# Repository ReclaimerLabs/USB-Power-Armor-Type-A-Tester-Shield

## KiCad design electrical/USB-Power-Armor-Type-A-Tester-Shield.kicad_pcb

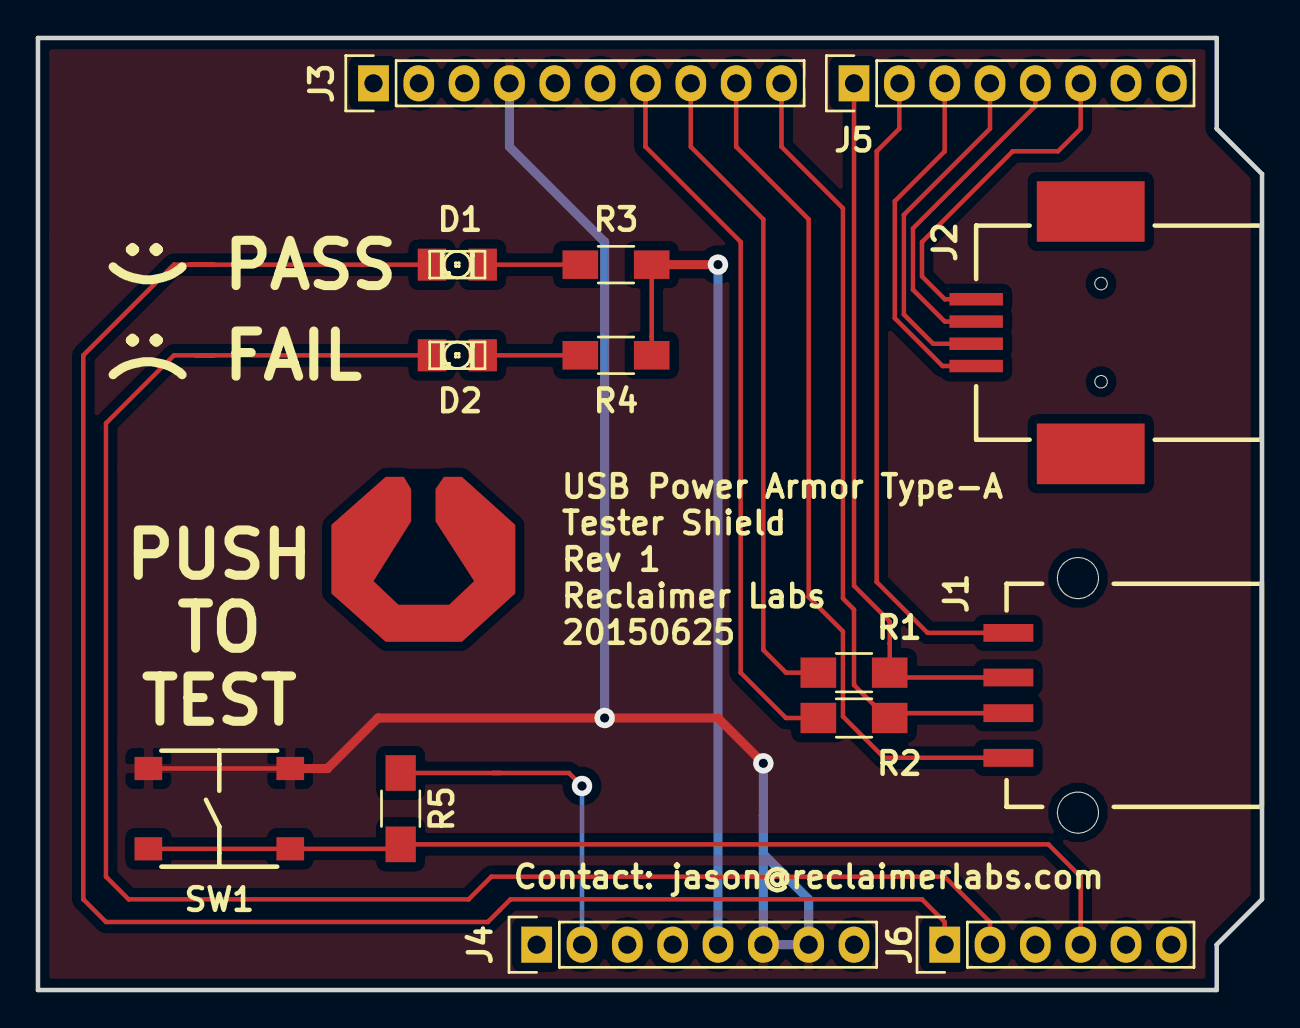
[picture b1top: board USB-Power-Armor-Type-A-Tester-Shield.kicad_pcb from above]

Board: 2 copper layers, 68.6 x 53.3 mm, 14 parts (0 on the bottom side), 18 nets.

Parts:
D1, D2: LED; LED-1206
J1: USB_A; USB_A_Female_SMD
J2: USB_B; USB-B_SMT_4pin
J3: CONN_01X10; Pin_Header_Straight_1x10
J4, J5: CONN_01X08; Pin_Header_Straight_1x08
J6: CONN_01X06; Pin_Header_Straight_1x06
R1, R2: 1M; R_1206_HandSoldering
R3, R4: 330R; C_1206_HandSoldering
R5: 10k; R_1206_HandSoldering
SW1: SW_PUSH; SW_Tact_PTS645S_SMD

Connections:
+5V: J4.5, R3.1, R4.1
/A0: D1.1, J6.1
/A1: D2.1, J6.2
/A3: J6.4, R5.2, SW1.2
/D2: J2.1, J5.6
/D3: J2.4, J5.5
/D4: J2.2, J5.4
/D5: J2.3, J5.3
/D6: J1.1, J5.2
/D7: J1.2, J5.1, R1.2
/D8: J1.3, J3.10, R2.2
/D9: J1.4, J3.9
/D10: J3.8, R1.1
/D11: J3.7, R2.1
/IOREF: J4.2, R5.1
GND: J3.4, J4.6, J4.7, SW1.1
unnamed: D1.2, R3.2
unnamed: D2.2, R4.2

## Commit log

2016-02-18 :confetti_ball: Added .gitattributes
2016-02-18 Initial Check-in
